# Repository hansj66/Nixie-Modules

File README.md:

This repository holds a Collection of Eagle schematics and board layouts for driving Nixie and VFD display tubes.
These schematics are not yet verified. The IN-12 Arduino and Raspberry Shields are tested ok. The remaining modules are still in development.

# IN-12-Raspberry Pi Zero W Shield

This is a 6 tube shield that connects to the GPIO header of a Raspberry Pi Zero W. 

A video of the shield running the clock.c driver can be found here: https://youtu.be/0auW9YwZaXU

# IN-12-Arduino Shield 

A video of the shield running the code sample can be found here: https://youtu.be/qcBPYD-F15M

The shield has 4 IN-12 Nixie tubes. The shield requires external 170V power. 5V is obtained via the shield connector. Pin mapping is as follows

## Parts list:

- 4 x IN-12 tubes.
- 4 x K155ID1.
- 2 x 74HC595.
- 4 x anode resistors. The value of these should be calculated according to tube rating and drive voltage.
- 5 x pushbutton switches (optional).  

### Arduino pin mapping
- D0: SER
- D1: RCLK
- D2: SER
- D8-D12: optional switches.  

# IN-2 Nixie-Modules
Each Module has two Nixie tubes, a shift register and a nixie driver. The modules require external 5V/170V power. The on-board shift registeres allows the modules to be daisy chained.  

## Parts list:
- 2 x IN-2 tubes.
- 2 x K155ID1.
- 1 x 74HC595.
- 2 x anode resistors. The value of these should be calculated according to tube rating and drive voltage.  

# TimeExpander Eagle Library
The librar contains Eagle symbol, package and device definitions for K155ID1 (pin compatible with the obsolete 74141) along with the following display tubes:  
- IN-1 - not verified
- IN-2 - verified
- IN-12 - verified
- IV-12 - not verified
- IV-22 - not verified

# IN-1-Modules
TBD

# VFD-Modules
TBD

Hans Jørgen Grimstad
www.TimeExpander.com

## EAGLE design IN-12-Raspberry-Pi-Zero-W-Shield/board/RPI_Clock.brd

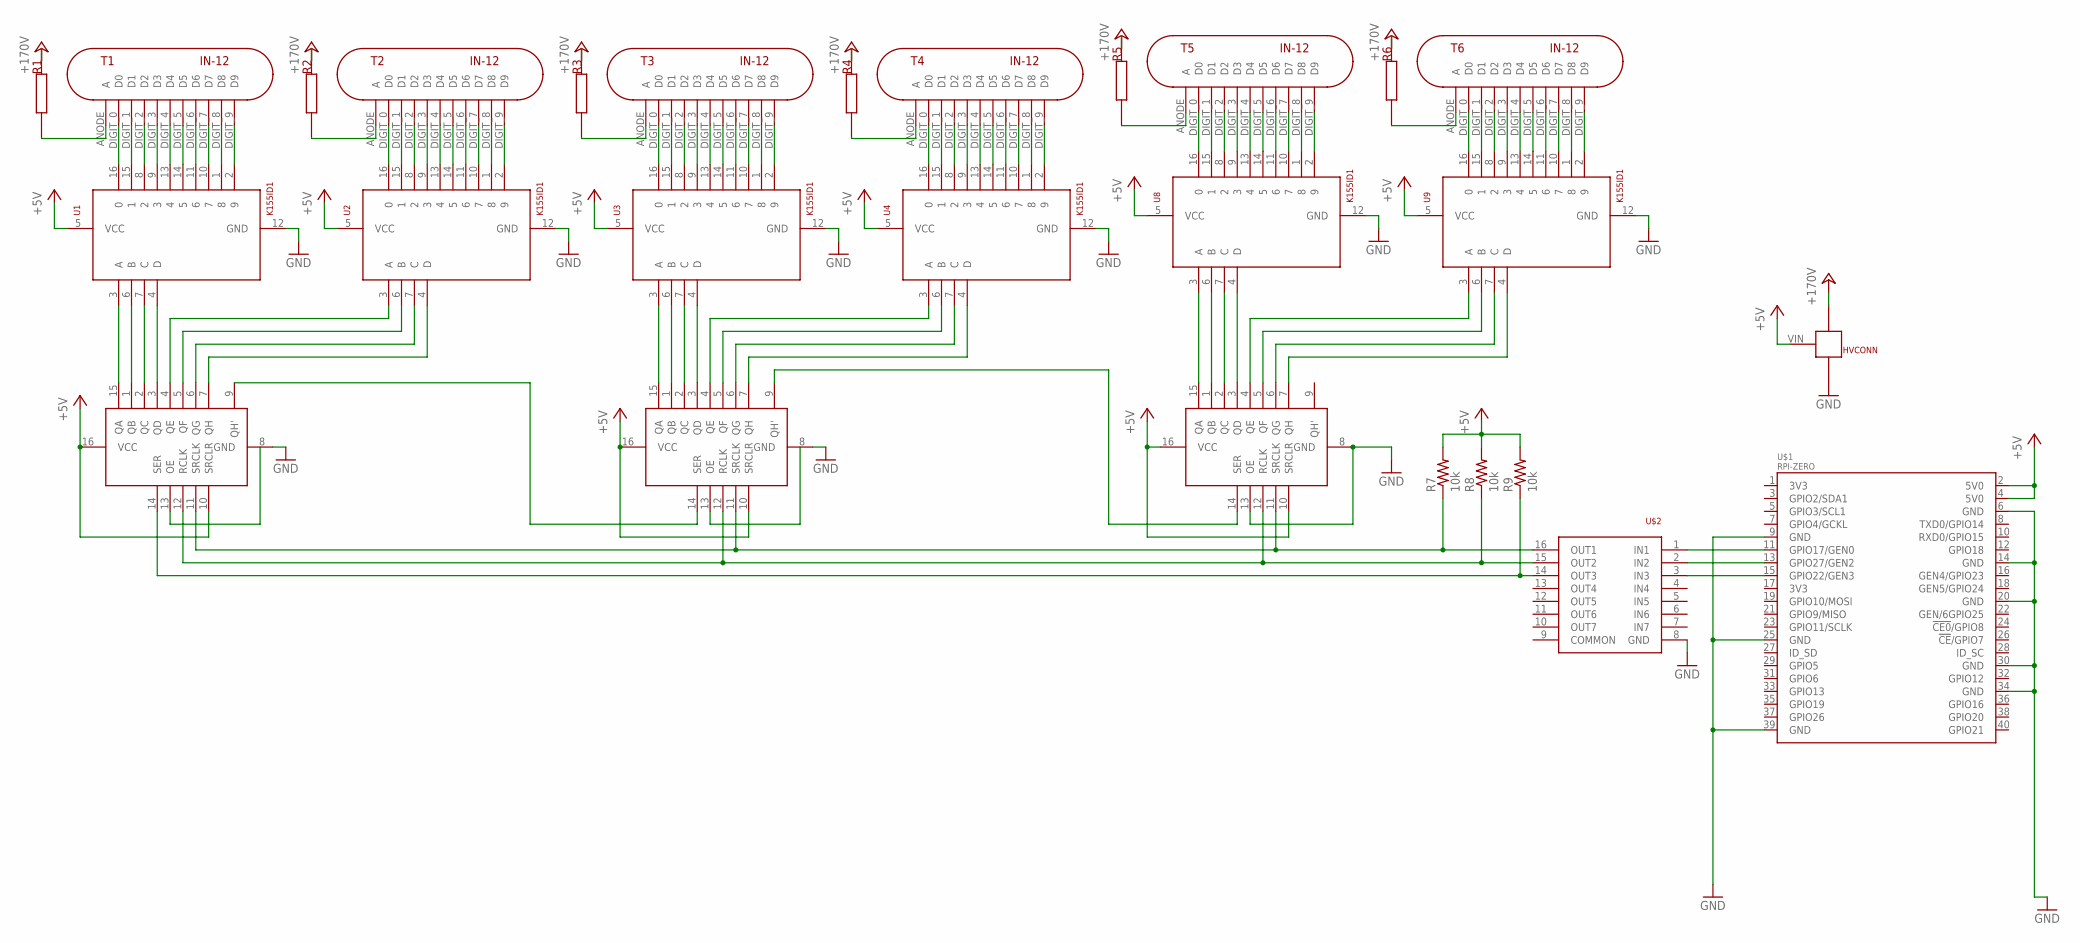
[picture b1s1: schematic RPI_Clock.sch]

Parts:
HVCONN: HV_CONNECTOR
R1, R2, R3, R4, R5, R6: 5,6K; ANODE_RESISTOR
R7, R8, R9: 10k; 0805
T1, T2, T3, T4, T5, T6: IN-12
U1, U2, U3, U4, U8, U9: K155ID1; DIP16-2.54-19.2X7.62MM
U6, U7, U11: 74HC595; DIL16
U$1: RPI-ZERO; RASP_PI_ZERO_BOARD_FULL
U$2: ULN2003D1013TR; SO16-NARROW

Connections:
+5V: HVCONN.VIN, R7.2, R8.2, R9.2, U1.5 (VCC), U2.5 (VCC), U3.5 (VCC), U4.5 (VCC), U6.10 (SRCLR), U6.16 (VCC), U7.10 (SRCLR), U7.16 (VCC), U8.5 (VCC), U9.5 (VCC), U11.10 (SRCLR), U11.16 (VCC), U$1.2 (5V0), U$1.4 (5V0)
+24V: HVCONN.+170V, R1.P$2, R2.P$2, R3.P$2, R4.P$2, R5.P$2, R6.P$2
GND: HVCONN.GND, U1.12 (GND), U2.12 (GND), U3.12 (GND), U4.12 (GND), U6.8 (GND), U7.8 (GND), U8.12 (GND), U9.12 (GND), U11.8 (GND), U11.13 (OE), U$1.6 (GND), U$1.9 (GND), U$1.14 (GND), U$1.20 (GND), U$1.25 (GND), U$1.30 (GND), U$1.34 (GND), U$1.39 (GND), U$2.8 (GND)
unnamed: T1.DIGIT_9 (D9), U1.2 (9)
unnamed: T1.DIGIT_8 (D8), U1.1 (8)
unnamed: T1.DIGIT_7 (D7), U1.10 (7)
unnamed: T1.DIGIT_6 (D6), U1.11 (6)
unnamed: T1.DIGIT_5 (D5), U1.14 (5)
unnamed: T1.DIGIT_4 (D4), U1.13 (4)
unnamed: T1.DIGIT_3 (D3), U1.9 (3)
unnamed: T1.DIGIT_2 (D2), U1.8 (2)
unnamed: T1.DIGIT_1 (D1), U1.15 (1)
unnamed: T1.DIGIT_0 (D0), U1.16 (0)
unnamed: R1.P$1, T1.ANODE (A)
unnamed: T2.DIGIT_9 (D9), U2.2 (9)
unnamed: T2.DIGIT_8 (D8), U2.1 (8)
unnamed: T2.DIGIT_7 (D7), U2.10 (7)
unnamed: T2.DIGIT_6 (D6), U2.11 (6)
unnamed: T2.DIGIT_5 (D5), U2.14 (5)
unnamed: T2.DIGIT_4 (D4), U2.13 (4)
unnamed: T2.DIGIT_3 (D3), U2.9 (3)
unnamed: T2.DIGIT_2 (D2), U2.8 (2)
unnamed: T2.DIGIT_1 (D1), U2.15 (1)
unnamed: T2.DIGIT_0 (D0), U2.16 (0)
unnamed: R2.P$1, T2.ANODE (A)
unnamed: T3.DIGIT_9 (D9), U3.2 (9)
unnamed: T3.DIGIT_8 (D8), U3.1 (8)
unnamed: T3.DIGIT_7 (D7), U3.10 (7)
unnamed: T3.DIGIT_6 (D6), U3.11 (6)
unnamed: T3.DIGIT_5 (D5), U3.14 (5)
unnamed: T3.DIGIT_4 (D4), U3.13 (4)
unnamed: T3.DIGIT_3 (D3), U3.9 (3)
unnamed: T3.DIGIT_2 (D2), U3.8 (2)
unnamed: T3.DIGIT_1 (D1), U3.15 (1)
unnamed: T3.DIGIT_0 (D0), U3.16 (0)
unnamed: R3.P$1, T3.ANODE (A)
unnamed: T4.DIGIT_9 (D9), U4.2 (9)
unnamed: T4.DIGIT_8 (D8), U4.1 (8)
unnamed: T4.DIGIT_7 (D7), U4.10 (7)
unnamed: T4.DIGIT_6 (D6), U4.11 (6)
unnamed: T4.DIGIT_5 (D5), U4.14 (5)
unnamed: T4.DIGIT_4 (D4), U4.13 (4)
unnamed: T4.DIGIT_3 (D3), U4.9 (3)
unnamed: T4.DIGIT_2 (D2), U4.8 (2)
unnamed: T4.DIGIT_1 (D1), U4.15 (1)
unnamed: T4.DIGIT_0 (D0), U4.16 (0)
unnamed: R4.P$1, T4.ANODE (A)
unnamed: U$1.11 (GPIO17/GEN0), U$2.1 (IN1)
unnamed: U$1.13 (GPIO27/GEN2), U$2.2 (IN2)
unnamed: R7.1, U6.11 (SRCLK), U7.11 (SRCLK), U11.11 (SRCLK), U$2.16 (OUT1)
unnamed: R8.1, U6.12 (RCLK), U7.12 (RCLK), U11.12 (RCLK), U$2.15 (OUT2)
unnamed: R9.1, U6.14 (SER), U$2.14 (OUT3)
unnamed: U$1.15 (GPIO22/GEN3), U$2.3 (IN3)
unnamed: T5.DIGIT_9 (D9), U8.2 (9)
unnamed: T5.DIGIT_8 (D8), U8.1 (8)
unnamed: T5.DIGIT_7 (D7), U8.10 (7)
unnamed: T5.DIGIT_6 (D6), U8.11 (6)
unnamed: T5.DIGIT_5 (D5), U8.14 (5)
unnamed: T5.DIGIT_4 (D4), U8.13 (4)
unnamed: T5.DIGIT_3 (D3), U8.9 (3)
unnamed: T5.DIGIT_2 (D2), U8.8 (2)
unnamed: T5.DIGIT_1 (D1), U8.15 (1)
unnamed: T5.DIGIT_0 (D0), U8.16 (0)
unnamed: R5.P$1, T5.ANODE (A)
unnamed: U1.3 (A), U6.15 (QA)
unnamed: U1.6 (B), U6.1 (QB)
unnamed: U1.7 (C), U6.2 (QC)
unnamed: U1.4 (D), U6.3 (QD)
unnamed: U2.3 (A), U6.4 (QE)
unnamed: U2.6 (B), U6.5 (QF)
unnamed: U2.7 (C), U6.6 (QG)
unnamed: U2.4 (D), U6.7 (QH)
unnamed: U3.3 (A), U7.15 (QA)
unnamed: U3.6 (B), U7.1 (QB)
unnamed: U3.7 (C), U7.2 (QC)
unnamed: U3.4 (D), U7.3 (QD)
unnamed: U4.3 (A), U7.4 (QE)
unnamed: U4.6 (B), U7.5 (QF)
unnamed: U4.7 (C), U7.6 (QG)
unnamed: U4.4 (D), U7.7 (QH)
unnamed: T6.DIGIT_9 (D9), U9.2 (9)
unnamed: T6.DIGIT_8 (D8), U9.1 (8)
unnamed: T6.DIGIT_7 (D7), U9.10 (7)
unnamed: T6.DIGIT_6 (D6), U9.11 (6)
unnamed: T6.DIGIT_5 (D5), U9.14 (5)
unnamed: T6.DIGIT_4 (D4), U9.13 (4)
unnamed: T6.DIGIT_3 (D3), U9.9 (3)
unnamed: T6.DIGIT_2 (D2), U9.8 (2)
unnamed: U6.9 (QH'), U7.14 (SER)
unnamed: T6.DIGIT_1 (D1), U9.15 (1)
unnamed: T6.DIGIT_0 (D0), U9.16 (0)
unnamed: R6.P$1, T6.ANODE (A)
unnamed: U8.3 (A), U11.15 (QA)
unnamed: U8.6 (B), U11.1 (QB)
unnamed: U8.7 (C), U11.2 (QC)
unnamed: U8.4 (D), U11.3 (QD)
unnamed: U9.3 (A), U11.4 (QE)
unnamed: U9.6 (B), U11.5 (QF)
unnamed: U9.7 (C), U11.6 (QG)
unnamed: U9.4 (D), U11.7 (QH)
unnamed: U7.9 (QH'), U11.14 (SER)

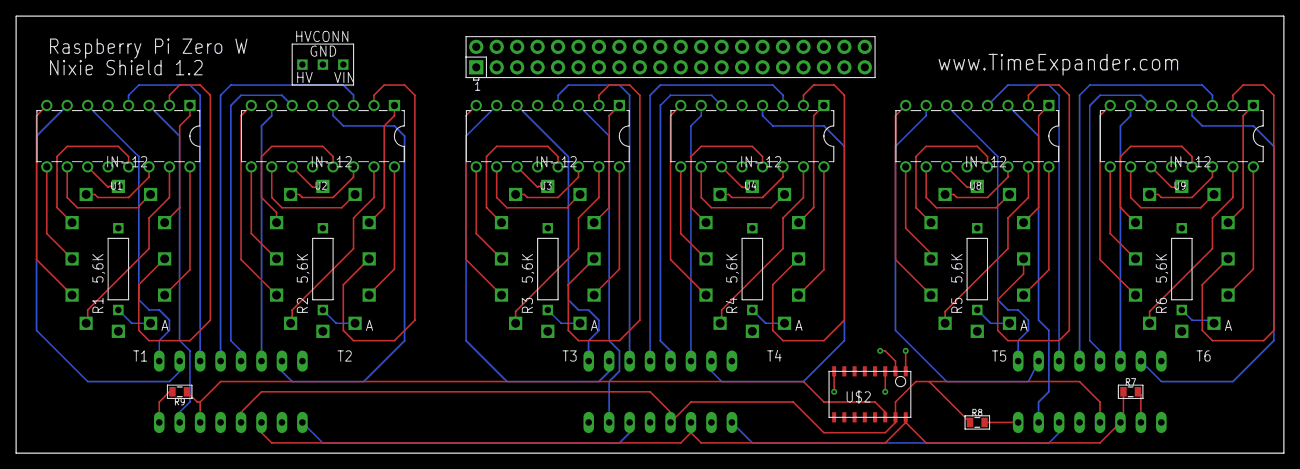
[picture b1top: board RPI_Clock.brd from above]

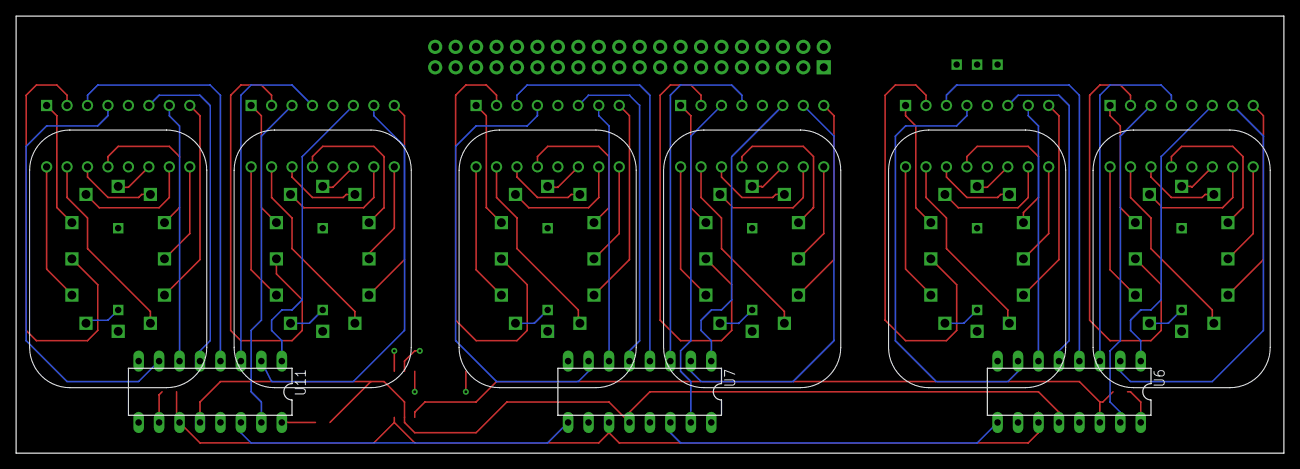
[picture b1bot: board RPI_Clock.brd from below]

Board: 4 copper layers, 157.5 x 54.3 mm, 27 parts (3 on the bottom side), 101 nets.

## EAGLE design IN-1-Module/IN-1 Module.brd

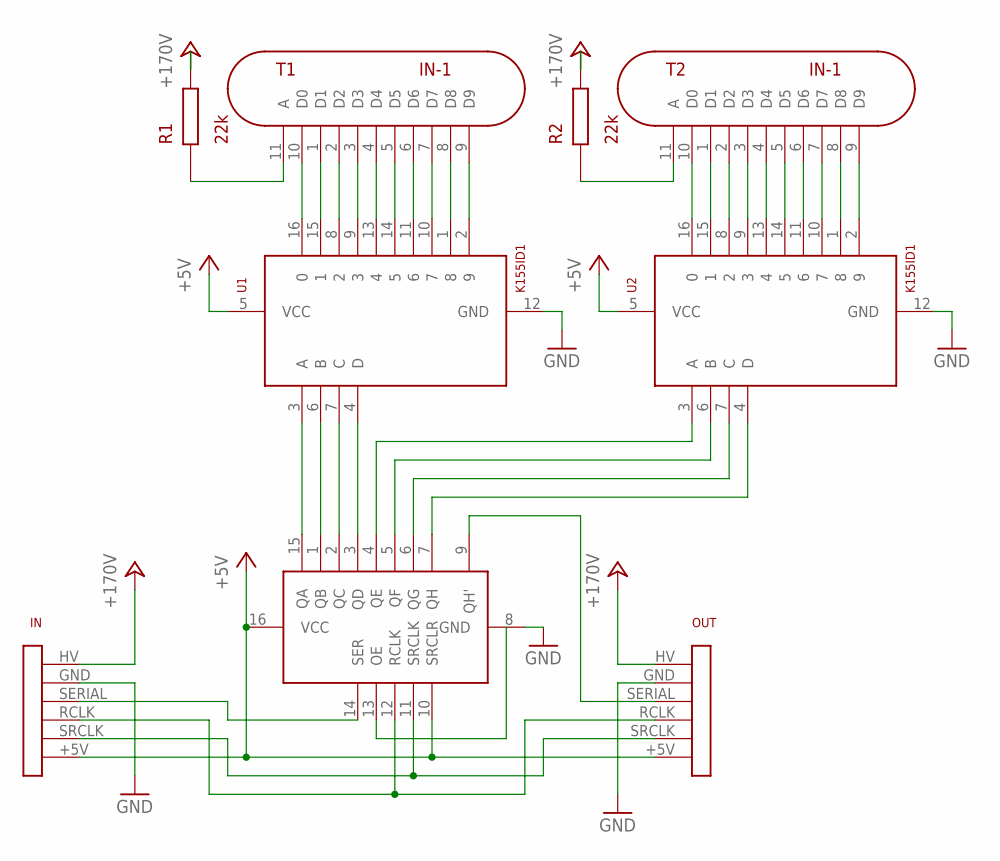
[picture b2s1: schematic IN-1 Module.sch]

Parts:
IN: NIXIE_INTERCONNECT
OUT: NIXIE_INTERCONNECT
R1, R2: 22k; ANODE_RESISTOR
T1, T2: IN-1
U1, U2: K155ID1; DIP16-2.54-19.2X7.62MM
U3: 74HC595; DIL16

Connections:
+5V: IN.+5V, OUT.+5V, U1.5 (VCC), U2.5 (VCC), U3.10 (SRCLR), U3.16 (VCC)
+24V: IN.HV, OUT.HV, R1.P$2, R2.P$2
GND: IN.GND, OUT.GND, U1.12 (GND), U2.12 (GND), U3.8 (GND)
unnamed: R1.P$1, T1.11 (A)
unnamed: T1.10 (D0), U1.16 (0)
unnamed: T1.1 (D1), U1.15 (1)
unnamed: T1.2 (D2), U1.8 (2)
unnamed: T1.3 (D3), U1.9 (3)
unnamed: T1.4 (D4), U1.13 (4)
unnamed: T1.5 (D5), U1.14 (5)
unnamed: T1.6 (D6), U1.11 (6)
unnamed: T1.7 (D7), U1.10 (7)
unnamed: T1.8 (D8), U1.1 (8)
unnamed: T1.9 (D9), U1.2 (9)
unnamed: R2.P$1, T2.11 (A)
unnamed: T2.10 (D0), U2.16 (0)
unnamed: T2.1 (D1), U2.15 (1)
unnamed: T2.2 (D2), U2.8 (2)
unnamed: T2.3 (D3), U2.9 (3)
unnamed: T2.4 (D4), U2.13 (4)
unnamed: T2.5 (D5), U2.14 (5)
unnamed: T2.6 (D6), U2.11 (6)
unnamed: T2.7 (D7), U2.10 (7)
unnamed: T2.8 (D8), U2.1 (8)
unnamed: T2.9 (D9), U2.2 (9)
unnamed: OUT.SERIAL, U3.9 (QH')
unnamed: IN.SERIAL, U3.14 (SER)
unnamed: IN.RCLK, OUT.RCLK, U3.12 (RCLK)
unnamed: IN.SRCLK, OUT.SRCLK, U3.11 (SRCLK)
unnamed: U1.3 (A), U3.15 (QA)
unnamed: U1.6 (B), U3.1 (QB)
unnamed: U1.7 (C), U3.2 (QC)
unnamed: U1.4 (D), U3.3 (QD)
unnamed: U2.3 (A), U3.4 (QE)
unnamed: U2.6 (B), U3.5 (QF)
unnamed: U2.7 (C), U3.6 (QG)
unnamed: U2.4 (D), U3.7 (QH)

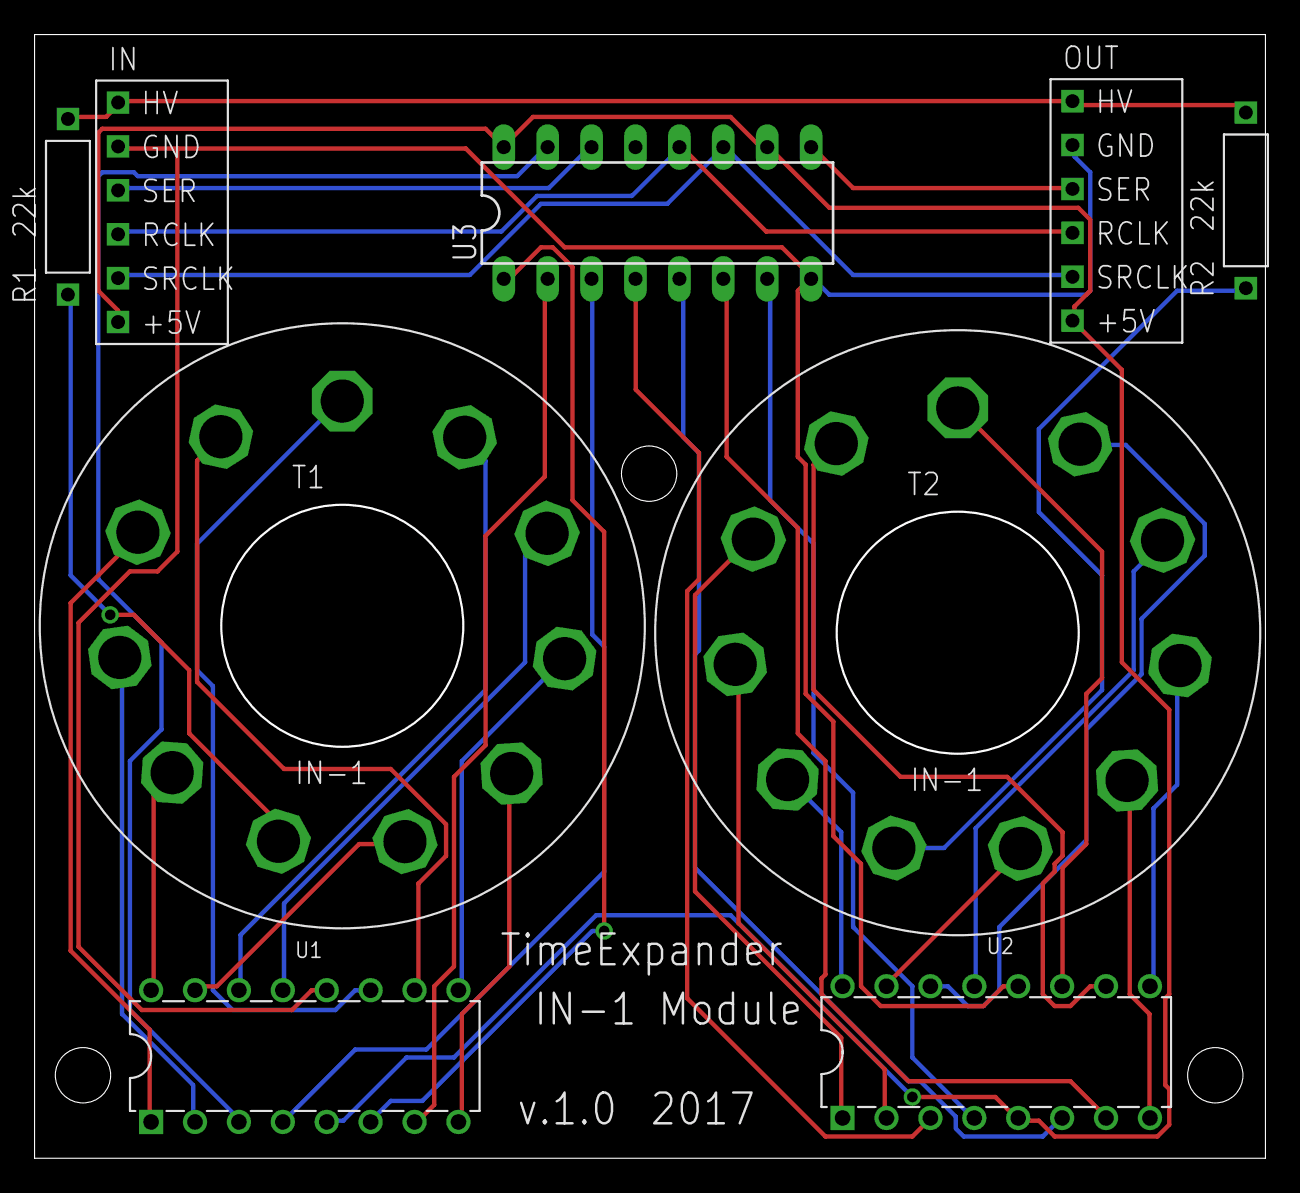
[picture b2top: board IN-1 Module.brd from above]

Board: 2 copper layers, 71.1 x 64.9 mm, 9 parts (0 on the bottom side), 37 nets.

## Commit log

2016-12-19 Added IN-12 shield, IN-1/2/12 Module, Eagle Library
2017-02-15 Fixed tube orientation. Added firmware example code.
2017-03-19 Updated interconnect package.
2017-04-01 Updated readme with IN-2 modules
2017-04-01 Added arduino example for IN-2 modules
2018-02-24 Added driver code for Raspberry Pi Zero W shield
2018-02-24 Added Eagle sch/brd and BoM for raspberry clock

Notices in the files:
README.md:
http://mirrors.creativecommons.org/presskit/buttons/88x31/png/by-nc-sa.png
